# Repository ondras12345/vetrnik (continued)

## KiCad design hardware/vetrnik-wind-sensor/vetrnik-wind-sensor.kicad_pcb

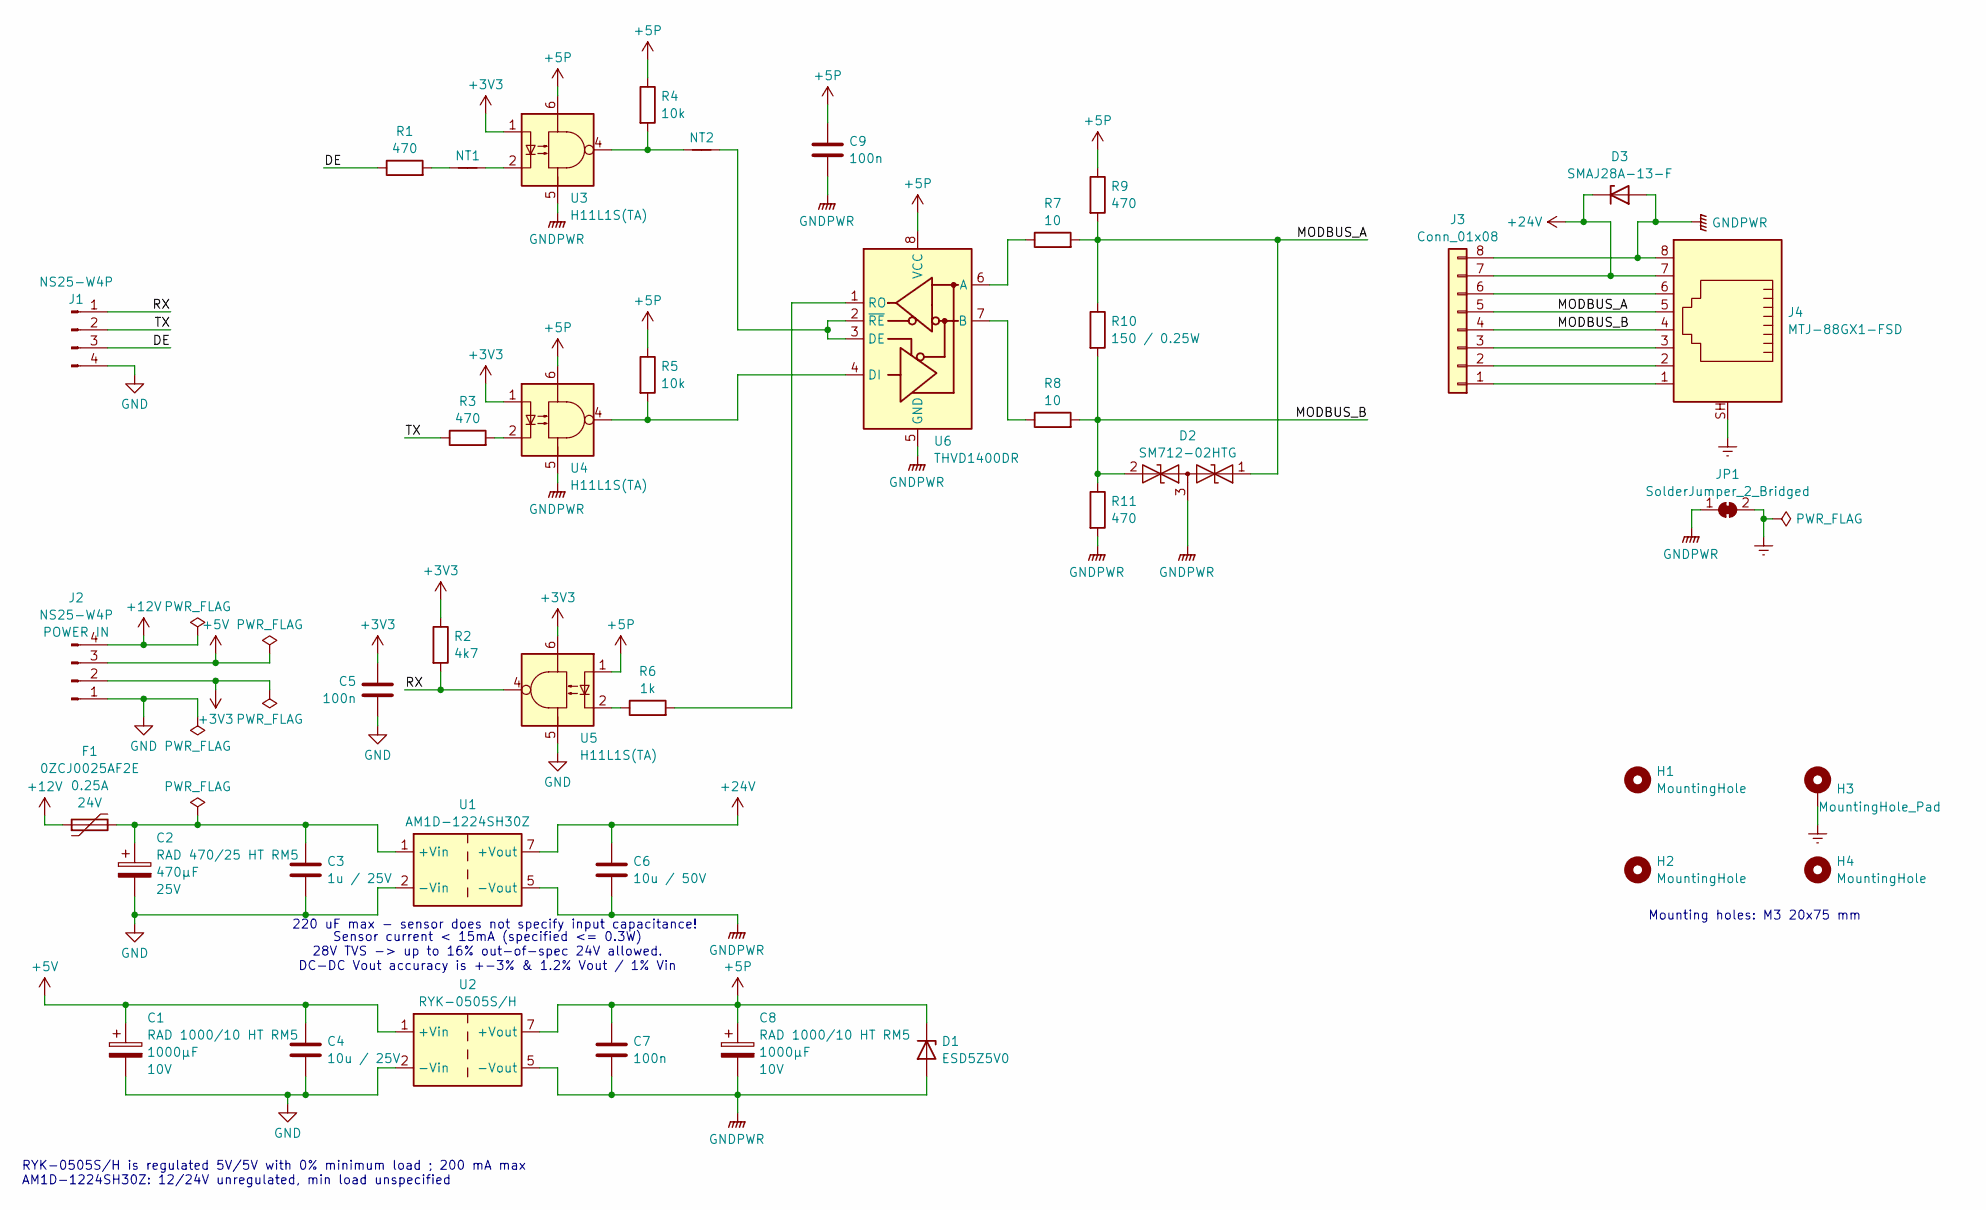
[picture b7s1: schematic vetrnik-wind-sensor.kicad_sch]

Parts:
C1, C8: RAD 1000/10 HT RM5; CP_Radial_D8.0mm_P5.00mm; Rated Voltage 10V
C2: RAD 470/25 HT RM5; CP_Radial_D10.0mm_P5.00mm; Rated Voltage 25V
C3: 1u / 25V; C_1206_3216Metric_Pad1.33x1.80mm_HandSolder
C4: 10u / 25V; C_1206_3216Metric_Pad1.33x1.80mm_HandSolder
C5, C7, C9: 100n; C_1206_3216Metric_Pad1.33x1.80mm_HandSolder
C6: 10u / 50V; C_1206_3216Metric_Pad1.33x1.80mm_HandSolder
D1: ESD5Z5V0; D_SOD-523; Breakdown Voltage 6.2V; Forward Voltage 6.2V
D2: SM712-02HTG; SOT-23; Breakdown Voltage 7.5...13.3V; Forward Voltage 7.5...13.3V
D3: SMAJ28A-13-F; D_SMA_Handsoldering; Breakdown Voltage 31.1...34.4V; Forward Voltage 31.1...34.4V
F1: 0ZCJ0025AF2E; Fuse_1206_3216Metric_Pad1.42x1.75mm_HandSolder; Rated Voltage 24V
H1, H2, H4: MountingHole; MountingHole_3.2mm_M3
H3: MountingHole_Pad; MountingHole_3.2mm_M3_Pad
J1, J2: NS25-W4P; Molex_KK-254_AE-6410-04A_1x04_P2.54mm_Vertical; Rated Voltage 0.25kV
J3: Conn_01x08; PinHeader_1x08_P2.54mm_Vertical
J4: MTJ-88GX1-FSD; RJ45_HALO_HFJ11-x2450HRL_Horizontal
JP1: SolderJumper_2_Bridged; R_1206_3216Metric_Pad1.30x1.75mm_HandSolder
NT1, NT2: NetTie_2; R_1206_3216Metric_Pad1.30x1.75mm_HandSolder
R1, R3, R9, R11: 470; R_1206_3216Metric_Pad1.30x1.75mm_HandSolder
R2: 4k7; R_1206_3216Metric_Pad1.30x1.75mm_HandSolder
R4, R5: 10k; R_1206_3216Metric_Pad1.30x1.75mm_HandSolder
R6: 1k; R_1206_3216Metric_Pad1.30x1.75mm_HandSolder
R7, R8: 10; R_1206_3216Metric_Pad1.30x1.75mm_HandSolder
R10: 150 / 0.25W; R_1206_3216Metric_Pad1.30x1.75mm_HandSolder
U1: AM1D-1224SH30Z; Converter_DCDC_TRACO_TEA1-xxxxHI_THT; Input Voltage 10.8...13.2V DC; Output Voltage 24V DC
U2: RYK-0505S/H; Converter_DCDC_TRACO_TEA1-xxxxHI_THT; Input Voltage 5V DC; Output Voltage 5V DC
U3, U4, U5: H11L1S(TA); SMDIP-6_W9.53mm
U6: THVD1400DR; SOIC-8_3.9x4.9mm_P1.27mm; Supply Voltage 3...5.5V DC

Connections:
+3V3: C5.1, J2.2, R2.1, U3.1, U4.1, U5.6
+5P: C7.1, C8.1, C9.1, D1.1 (K), R4.1, R5.1, R9.1, U2.7 (+Vout), U3.6, U4.6, U5.1, U6.8 (VCC)
+5V: C1.1, C4.1, J2.3, U2.1 (+Vin)
+12V: F1.1, J2.4
+24V: C6.1, D3.1 (K), J3.7, J4.7, U1.7 (+Vout)
/DE: J1.3, R1.1
/MODBUS_A: D2.1 (A1), J3.5, J4.5, R7.2, R9.2, R10.1
/MODBUS_B: D2.2 (A2), J3.4, J4.4, R8.2, R10.2, R11.1
/RX: J1.1, R2.2, U5.4
/TX: J1.2, R3.1
Earth: H3.1, J4.SH, JP1.2 (B)
GND: C1.2, C2.2, C3.2, C4.2, C5.2, J1.4, J2.1, U1.2 (-Vin), U2.2 (-Vin), U5.5
GNDPWR: C6.2, C7.2, C8.2, C9.2, D1.2 (A), D2.3 (common), D3.2 (A), J3.8, J4.8, JP1.1 (A), R11.2, U1.5 (-Vout), U2.5 (-Vout), U3.5, U4.5, U6.5 (GND)
unnamed: J3.1, J4.1
unnamed: J3.2, J4.2
unnamed: J3.3, J4.3
unnamed: J3.6, J4.6
unnamed: NT1.1, R1.2
unnamed: NT1.2, U3.2
unnamed: NT2.1, R4.2, U3.4
unnamed: R3.2, U4.2
unnamed: R6.1, U5.2
unnamed: C2.1, C3.1, F1.2, U1.1 (+Vin)
unnamed: R7.1, U6.6 (A)
unnamed: R8.1, U6.7 (B)
unnamed: NT2.2, U6.2 (~RE), U6.3 (DE)
unnamed: R5.2, U4.4, U6.4 (DI)
unnamed: R6.2, U6.1 (RO)

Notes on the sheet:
Sensor current < 15mA (specified <= 0.3W) 28V TVS -> up to 16% out-of-spec 24V allowed. DC-DC Vout accuracy is +-3% & 1.2% Vout / 1% Vin
RYK-0505S/H is regulated 5V/5V with 0% minimum load ; 200 mA max AM1D-1224SH30Z: 12/24V unregulated, min load unspecified
Mounting holes: M3 20x75 mm
220 uF max - sensor does not specify input capacitance!

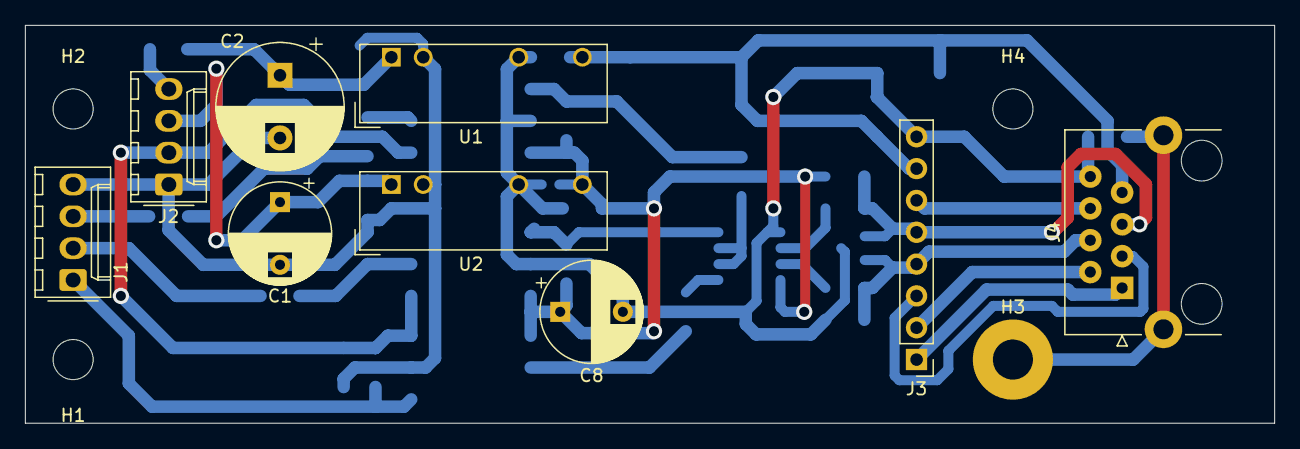
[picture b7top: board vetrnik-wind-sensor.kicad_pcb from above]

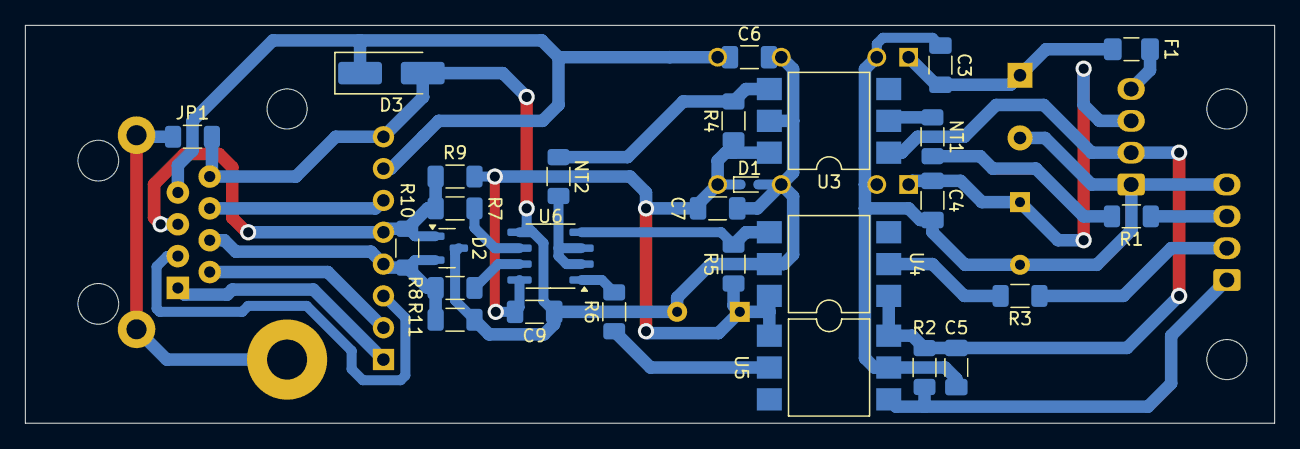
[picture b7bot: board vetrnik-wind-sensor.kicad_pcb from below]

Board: 2 copper layers, 99.7 x 31.8 mm, 41 parts (28 on the bottom side), 28 nets.

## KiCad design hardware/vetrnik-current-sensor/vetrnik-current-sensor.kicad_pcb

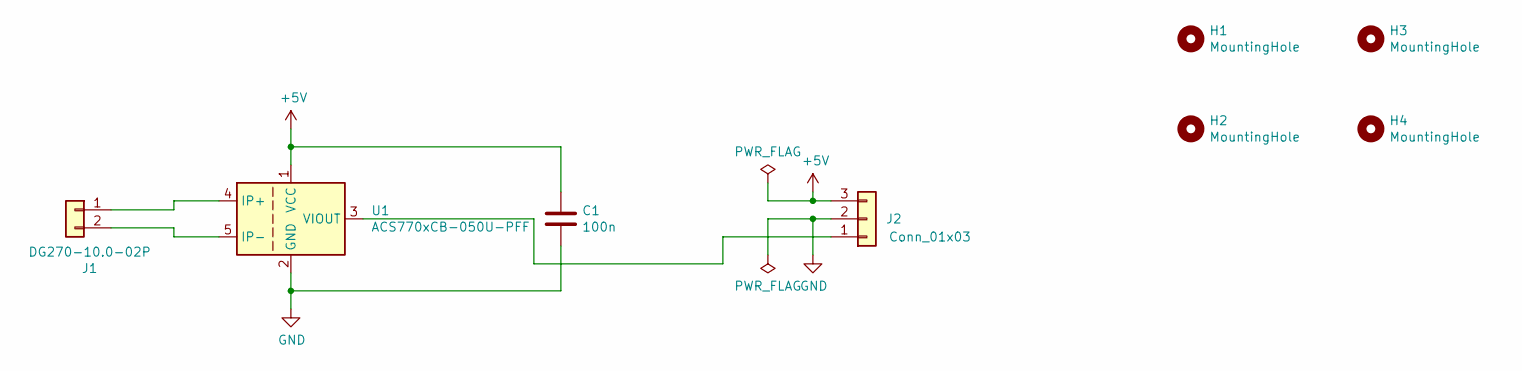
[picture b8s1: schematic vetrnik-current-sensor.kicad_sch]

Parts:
C1: 100n; C_1206_3216Metric_Pad1.33x1.80mm_HandSolder
H1, H2, H3, H4: MountingHole; MountingHole_3.2mm_M3
J1: DG270-10.0-02P; DG270-10.0-02P-14-00A
J2: Conn_01x03; Molex_KK-254_AE-6410-03A_1x03_P2.54mm_Vertical
U1: ACS770xCB-050U-PFF; Allegro_CB_PFF

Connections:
+5V: C1.1, J2.3, U1.1 (VCC)
GND: C1.2, J2.2, U1.2 (GND)
unnamed: J1.1, U1.4 (IP+)
unnamed: J1.2, U1.5 (IP-)
unnamed: J2.1, U1.3 (VIOUT)

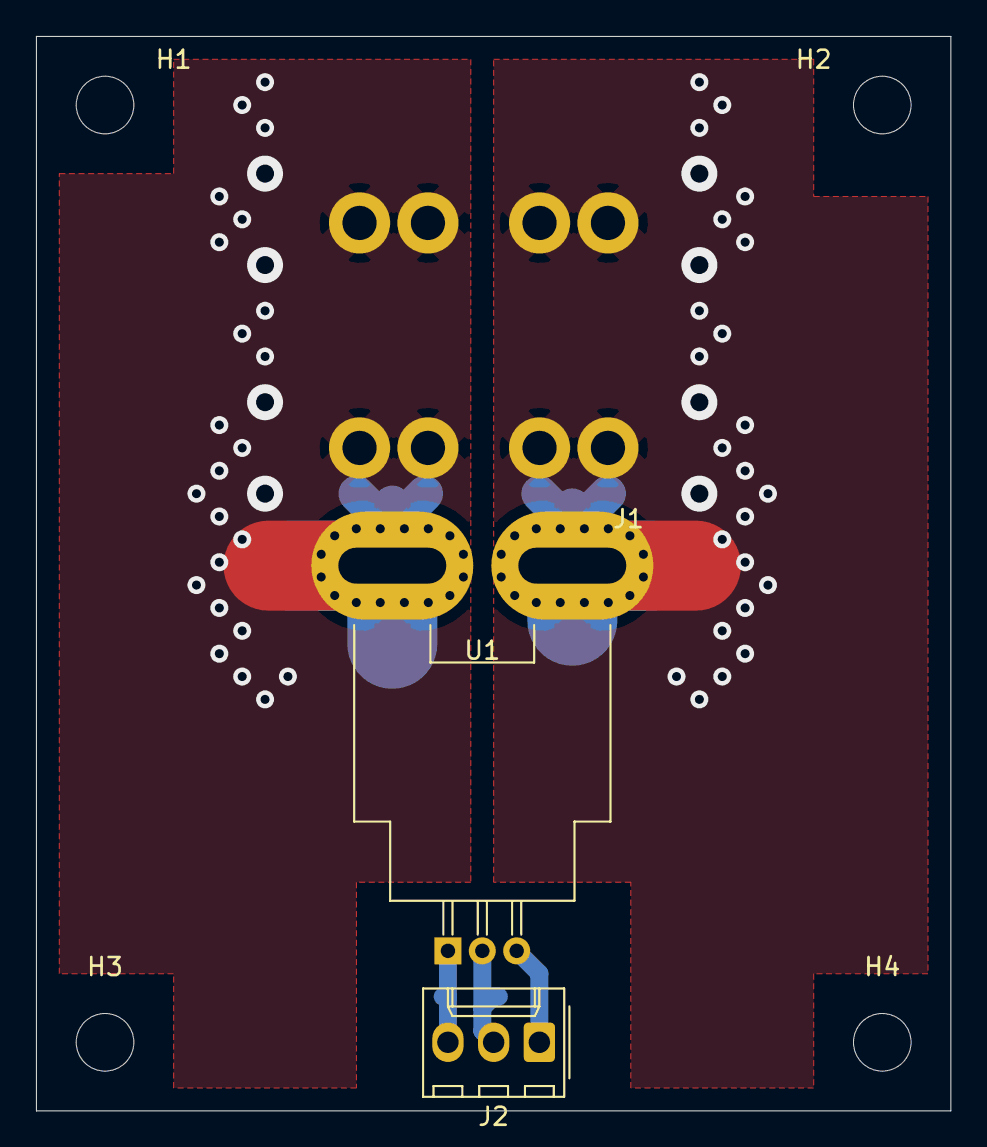
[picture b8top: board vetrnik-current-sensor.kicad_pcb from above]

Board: 2 copper layers, 50.8 x 59.7 mm, 8 parts (1 on the bottom side), 5 nets.

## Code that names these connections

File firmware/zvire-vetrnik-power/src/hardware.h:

#pragma once

#define pin_REL1        8   // PB0
#define pin_REL2        A5  // PC5
#define pin_REL3        A4  // PC4
#define pin_REL4        13  // PB5
#define pin_FAN         5   // PD5
#define pin_SHORT       6   // PD6, inverted

// See Hbridge.h
//#define pin_PWM1        9   // PB1
//#define pin_PWM2        10  // PB2
//#define pin_SD          7   // PD7, inverted

#define pin_VSENSE      A0  // PC0
#define pin_ACS712      A1  // PC1
#define pin_ACS712_2    A2  // PC2
#define pin_NTC1        A3  // PC3

// RPM is connected to two pins, but only pin_RPM_1 is used.
#define pin_RPM_1       2   // PD2
#define pin_RPM_2       4   // PD4
#define pin_ENABLE      3   // PD3, inverted

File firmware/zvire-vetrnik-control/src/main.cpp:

#include <Arduino.h>
#include "settings.h"

#ifdef WATCHDOG_TIME
#include <IWatchdog.h>
#endif

#include "uart_power.h"
#include "power_datapoints.h"
#include "mqtt.h"
#include "ota.h"
#include "cli.h"
#include "debug.h"
#include "power_board.h"
#include "lisp.h"
#include "control.h"
#include "stats.h"
#include "display.h"
#include "sensor_DS18B20.h"
#include "log.h"
#include "reset_cause.h"
#include <SerialFlash.h>
#include <Bounce2.h>


static Bounce2::Button button1 = Bounce2::Button();
static Bounce2::Button button2 = Bounce2::Button();


void setup()
{
    reset_cause_t reset_cause = reset_cause_get();
    log_init(
        reset_cause == RESET_CAUSE_BROWNOUT_RESET ||
        reset_cause == RESET_CAUSE_POWER_ON_POWER_DOWN_RESET
    );
    log_add_record_reboot(reset_cause);

    Serial.begin();
    log_add_INFO_backend(&Serial);

    button1.attach(PIN_BUTTON1, INPUT_PULLUP);
    button1.interval(BUTTON_DEBOUNCE);
    button1.setPressedState(LOW);
    button2.attach(PIN_BUTTON2, INPUT_PULLUP);
    button2.interval(BUTTON_DEBOUNCE);
    button2.setPressedState(LOW);

    pinMode(PIN_SHORT_SENSE, INPUT_PULLUP);
    pinMode(PIN_BUZZER, OUTPUT);
    pinMode(PIN_SHORT, OUTPUT);
    pinMode(PIN_LED, OUTPUT);
    // PIN_ONEWIRE is unused
    pinMode(PIN_REL1, OUTPUT);
    pinMode(PIN_REL2, OUTPUT);

    pinMode(PIN_ETH_RST, OUTPUT);
    ETH_reset();

    digitalWrite(PIN_BUZZER, HIGH);
    pinMode(LED_BUILTIN, OUTPUT);
    for (uint8_t i = 0; i < 4; i++)
    {
        digitalWrite(LED_BUILTIN, LOW);
        delay(100);
        digitalWrite(LED_BUILTIN, HIGH);
        delay(100);
    }
    INFO->print("Flash init: ");
    INFO->println(SerialFlash.begin(PIN_FLASH_SS));
    INFO->println("settings_init");
    INFO->flush();
    settings_init();
    INFO->flush();
    MQTT_init();
#ifdef WATCHDOG_TIME
    // Only do this after MQTT_init (DHCP is slow)
    IWatchdog.begin(WATCHDOG_TIME*1000UL);
#endif
    uart_power_init();
    control_init();
    sensor_DS18B20_init();
    lisp_init();
    control_init_lisp();
    INFO->println("boot");
    CLI_init();
    display_init();
    display_init_lisp();
    lisp_run_blind_file(LISP_INIT_FILENAME);

    digitalWrite(PIN_BUZZER, LOW);
}


void loop()
{
    unsigned long loop_start_millis = millis();
    button1.update();
    if (button1.released())
    {
        if (button1.previousDuration() < BUTTON_LONG)
        {
            lisp_run_blind("(btn1_short)");
        }
        else if (button1.previousDuration() >= BUTTON_LONG)
        {
            lisp_run_blind("(btn1_long)");
        }
    }
    button2.update();
    if (button2.released())
    {
        if (button2.previousDuration() < BUTTON_LONG)
        {
            lisp_run_blind("(btn2_short)");
        }
        else if (button2.previousDuration() >= BUTTON_LONG)
        {
            lisp_run_blind("(btn2_long)");
        }
    }

    power_datapoints_loop();
    bool status_complete = uart_power_loop();
    if (status_complete)
    {
        power_board_status = power_board_status_read();
        control_new_state();
        stats_new_state();
        static bool prev_emergency = false;
        if (power_board_status.emergency != prev_emergency)
        {
            prev_emergency = power_board_status.emergency;
            log_add_event(kPowerBoardEmergency);
        }
    }
    else if (power_board_status.valid &&
             millis() - power_board_status.retrieved_millis >= 2000UL)
    {
        log_add_event_and_println(kPowerBoardStatusTimeout, INFO);
        power_board_status.valid = false;
        control_new_state();
        stats_new_state();
    }

    sensor_DS18B20_loop();
    control_loop();
    CLI_loop();
    unsigned long loop_duration_mid = millis() - loop_start_millis;
    MQTT_loop();
    ota_loop();
    display_loop();

    unsigned long loop_duration = millis() - loop_start_millis;
    if (loop_duration >= 1500U)
    {
        log_add_record_slow_loop(loop_duration, loop_duration_mid);
    }

#ifdef WATCHDOG_TIME
    IWatchdog.reload();
#endif
}

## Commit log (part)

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2023-01-30 [control] Add lisp commands for control strategy
2023-01-30 [power] Faster ADC sampling
2023-01-30 [power] Disable debug mode
2023-01-31 [power] Move RMS filter processing to ISR
    | conditions | before | after |
    |:--------------|:----------------|:----------------|
    | d128 with cap | 10.370A (1.030) | 10.065A (1.007) |
    | d128 w/o cap | 10.614A (0.936) | 10.065A (0.936) |
    | d255 with cap | 16.653A (1.671) | 16.592A (1.661) |
    | d255 w/o cap | 16.531A (1.651) | 16.470A (1.647) |
2023-01-31 [control] Rename `mqtt_status` CLI cmnd to `mqtt`
2023-01-31 [control] Rename Stream_utils to Print_utils
2023-02-01 [control] Add Lisp handler functions for buttons
2023-02-03 [hardware] Add control board schematics
2023-02-04 [hardware] Design other PCBs
2023-02-08 [control] Set up GPIO outputs
2023-02-08 [control] Add #define for Ethernet reset pin
2023-02-08 [control] Set LCD backlight from lisp
2023-02-08 [control] Restore fe (lisp) gc after error
2023-02-08 [control] Control LED_BUILTIN from lisp
2023-02-09 [control] Improve error message in CLI
2023-02-09 [control] Set duty to 0 when started by btn1_long
2023-02-09 [control] Use ethernet reset pin
    Mostly just to prevent issues with noise that might occur when it's left
    floating.
    Even touching the pin with a DMM probe would cause a reset.
2023-02-09 [hardware] Resistor values in current-sensor-opamp
2023-02-10 [control] Improve MPPT algorithm
2023-02-11 [control] Update shellminator & commander
2023-02-12 [control] Make startup faster
2023-03-05 [power] Report emergency mode status
2023-03-05 [control] Support power board emergency mode
2023-03-09 [control] Automatically reset ETH if it gets stuck
2023-04-08 [control] Sense contactor state and handle e-stop
2023-04-08 Add info about contactor RC snubber
2023-04-28 [power] Optimize for code size
2023-04-28 [power] Use ATOMIC_BLOCK instead of saving SREG
2023-04-28 [power] Replace cli/sei with ATOMIC_FORCEON
2023-04-28 [power] Use avr/eeprom.h instead of Arduino EEPROM
    This saves about 192 bytes of FLASH space.
2023-04-28 [power] Add puncover target to Makefile
2023-04-28 [power] Reduce number of millis calls
2023-04-29 [power] Add settings for OCP limits
2023-04-29 [power] Update NTC immediately after boot
2023-04-29 [control] Add support for power board REL outputs
2023-04-29 [control] Add info about telnet to README.md
2023-04-29 [control] Update TODOs in lisp/31-control-MPTT
2023-06-16 [control] Add hysteresis to MQTT RPM
2023-06-25 [control] Group MQTT topics for temperatures
2023-07-17 [hardware] Add gitignore file
2023-07-17 [control] Publish DS18B20 temperatures via MQTT
2023-07-17 [control] Add initial support for DS18B20 sensors
2023-07-17 [control] Give fe more memory
    I didn't encounter any problems, but after experimenting with
    test_fe_utils I found that 8k might be pushing it.
    More memory should allow the GC to run less often.
2023-07-18 [control] Add rem test case to test_fe_utils
2023-07-18 [control] Add basic support for OTA fw update
2023-07-19 [power] Add software enable command
2023-07-19 [control] Fix CLIeditor end sequence detection
2023-07-21 [control] [LISP] Control sw_enable & pump
2023-07-24 [LISP] Fix error if t0 temperature is nil
2023-07-24 [control] Report power_board/power via MQTT
2023-07-25 [control] Fix MAKETMP_DECIMAL for uint32_t
2023-07-27 [hardware] Add info about cables
2023-07-27 [control] Update dependencies
2023-07-28 [control] Optimize MAKETMP_BOOL MQTT helper
2023-07-29 [control] Allow executing CLI commands via MQTT
2023-08-07 [control] Add Home Assistant config package
2023-08-16 [power] Make RPM filter configurable
2023-08-16 [power] Improve build system
2023-08-16 [power] Remove TODO comment
2023-08-30 [control] Quiet down HA notification automation
2023-09-01 Silence warnings from new version of cppcheck
2023-09-01 [control] Reduce socket timeout for MQTT
    This should hopefully allow us to respond to the power board in time.
2023-09-05 [control] Add first version of postmort
2023-09-05 [control] Fix printf format strings
2023-09-05 [control] Enable -Wall compiler warnings
2023-09-06 [control] Only print first 100 records in CLI log
2023-09-06 [control] Fix log printing bug
2023-09-17 [control] Log DS18B20 errors
2023-09-30 [control] Update HA configuration for 2023.9
2023-11-12 [control] Add id to HA automation
2023-12-08 Rename firmware projects
2023-12-08 Remove outdated gbrjob files
2023-12-08 Rename enclosure documentation
2023-12-08 Update README files
2023-12-22 [control] Fix printing of MQTT publish error log
2023-12-22 [control] Detect & log millis rollover
2023-12-22 [control] Fix potentially imprecise energy stats
2023-12-22 [control] Log last millis value before reset
2023-12-22 [control] Prevent immediate MQTT reconnect
2023-12-22 [control] Add energy_Ws to Home Assistant
2024-03-23 [control] Make reset cause name shorter
    The kReboot message wouldn't fit in 80-character buffer in log.cpp
2024-04-07 [hardware] Fix renamed library
2024-04-10 [hardware] Add info about enclosure mods
2024-06-25 Add patch for testing w/o DS18B20
2024-06-26 [control] Implement smarter contactor control
2024-06-26 [LISP] Check power mode in btn1_long
2024-06-26 [control] Refactor conf printing and parsing
2024-06-26 [control] Store settings in text file
2024-06-26 [control] Fix false error raised from LISP ctrls
2024-06-26 [control] Tolerate 0x00 at the start of init.lisp
2024-06-26 [control] Split SPIflash to multiple commands
    before split:
    RAM: [======= ] 67.1% (used 44004 bytes from 65536 bytes)
    Flash: [===== ] 48.6% (used 127396 bytes from 262144 bytes)
    after split:
    RAM: [======= ] 67.5% (used 44220 bytes from 65536 bytes)
    Flash: [===== ] 48.7% (used 127740 bytes from 262144 bytes)
2024-06-27 [control] Fix parsing of DS18B20 config
    It would fail to parse after dfu upload, was reading uninitialized
    memory.
2024-06-27 [power] Report reset reason on boot
2024-06-27 [power] Add setting for stopping RPM
2024-06-27 [control] Try to fix WDT reset on mqtt reinit
2024-06-27 [control] Fix cat sometimes drops start of line
2024-06-27 [power] Tolerate longer refresh interval
2024-06-27 [power] Fix PWM generation
2024-06-28 [power] Add info from RPM filter measurement
    This was measured with DC offset on Meratronik gen to ensure enough
    amplitude for 50 % duty at optocoupler output.
2024-06-28 [LISP] Update instructions
2024-06-28 [LISP] MQTT reinit via btn2_long
2024-07-02 [power] Update OVP constants
    Hardware OVP trip voltage was changed in last HW mod, this commit
    updates SW OVP accordingly.
2024-07-02 [control] Update settings comment
2024-08-23 [hardware] Add block diagram
2024-08-23 [hardware] Add block diagram PDF
2025-02-01 Update pre-commit-hooks
2025-02-01 Add flake8 check to pre-commit
2025-02-01 Add yamllint check to pre-commit
2025-02-01 Add more LISP tests
2025-02-01 Port fe_utils from C++ to C
2025-02-02 Move display lisp functions to a separate lib
2025-02-02 Use t instead of 1 as true value in LISP tests
2025-02-02 Fix incorrect LISP test
    Discovered by
    $ ./sil.py run ../vetrnik-control/lisp/tests/test_*.lisp
2025-02-02 Add missing header in SIL
    sil.py needs it
2025-02-02 Add more functions to SIL
2025-02-04 Add custom Modelica tools
2025-02-05 Create a Modelica package
2025-02-05 Set rectifier parameters in test3
    Setting Goff=2.5e-8 S results in extremely slow simulation,
    so I'll leave it off for now.
2025-02-06 Add function to call vetrnik-sil from Modelica
2025-02-06 Add implement '(ds18' in SIL
2025-02-06 Add model README
2025-02-07 Make lines in WindTurbine model shorter
2025-02-08 Improve diagram of test4 model
2025-02-10 Fix rectifier parameters in SIL model
2025-02-11 Add icon to vetrnikController
2025-02-13 [LISP] Improve MPPT
    ... based on SILsimplified simulations.
    However, the original algorithm might have some advantages.
    It might be able to operate with a higher sampling rate.
2025-02-17 [LISP] Fix incorrect spec for pwrg
2025-02-21 Increase LISP memory size
2025-02-21 Improve MQTT_reinit watchdog fix
2025-02-21 Retry Ethernet even if eth_skip
2025-02-21 Fix missing pinMode in sensor_wind
2025-02-21 Handle errors in SIL REPL
2025-02-22 Add missing header include to reset_cause
    This will prevent the build from failing when ststm32 is updated.
    ststm32@15.6.0
    RAM: [======== ] 81.5% (used 53396 bytes from 65536 bytes)
    Flash: [===== ] 49.6% (used 129944 bytes from 262144 bytes)
    ststm32@16.0.0
    RAM: [======== ] 81.5% (used 53396 bytes from 65536 bytes)
2025-02-22 [power] Increase duty gradually in stopping mode
2025-02-23 [power] Do not require enable to start
2025-02-23 [control] Support larger MQTT messages
2025-03-01 Add temperature sensor to block diagram
    ...and rotate "G" in the generator symbol
2025-04-05 [model] Add diagrams to gitignore
2025-04-05 [model] Add SimplifiedOpenLoopTest.mo
2025-04-05 [model] Enable raiseerrors in linearize.py
2025-04-06 [model] Move Result to a separate .py file
    This should make it possible to import without having OMPython
    installed.
2025-04-06 [model] Add tool for diffing linearized models
2025-04-12 [model] Add models from testing
    I've created these quite some time ago, and while they aren't
    immediately useful, I don't want to delete them.
2025-04-12 Rename modes
2025-04-12 [lisp] Add test for (pwrs "mode" ...)
2025-04-12 Rename power modes in homeassistant config
2025-04-12 [control] s/PIN_SHORT_SENSE/PIN_CONTACTOR_SENSE/
2025-04-12 [control] Rename kControlShortEstop to kControlEstop
2025-04-12 [control] Use HAL functions in CLI
    before:
    RAM: [======== ] 81.5% (used 53392 bytes from 65536 bytes)
    Flash: [===== ] 49.6% (used 130136 bytes from 262144 bytes)
    after:
    RAM: [======== ] 81.5% (used 53392 bytes from 65536 bytes)
    Flash: [===== ] 49.7% (used 130200 bytes from 262144 bytes)
2025-04-12 [control] Update architecture overview in README
2025-04-18 [model] Add model for SIL with CSV input
2025-04-18 [control] Add pow function to lisp
2025-04-19 [lisp] Use a symlink to select MPPT controller
    Renaming files to *.disabled does not play nice with git.
2025-04-19 [control] Reduce flash usage
    ... by concatenating topic strings at runtime
    before:
    RAM: [======== ] 81.5% (used 53400 bytes from 65536 bytes)
    Flash: [===== ] 50.7% (used 132948 bytes from 262144 bytes)
    after:
    RAM: [======== ] 81.5% (used 53400 bytes from 65536 bytes)
2025-04-19 [control] Reduce flash usage
    before:
    RAM: [======== ] 81.5% (used 53412 bytes from 65536 bytes)
    Flash: [===== ] 50.7% (used 132796 bytes from 262144 bytes)
    after:
    RAM: [======== ] 81.5% (used 53412 bytes from 65536 bytes)
    Flash: [===== ] 50.5% (used 132404 bytes from 262144 bytes)
2025-04-19 Revert to inline MQTT command handlers
    before:
    RAM: [======== ] 81.5% (used 53412 bytes from 65536 bytes)
    Flash: [===== ] 50.5% (used 132340 bytes from 262144 bytes)
    after:
    RAM: [======== ] 81.5% (used 53412 bytes from 65536 bytes)
    Flash: [===== ] 50.5% (used 132268 bytes from 262144 bytes)
2025-04-19 [control] Reduce flash usage in MQTT handler
    before:
    RAM: [======== ] 81.5% (used 53412 bytes from 65536 bytes)
    Flash: [===== ] 50.4% (used 132100 bytes from 262144 bytes)
    after:
    RAM: [======== ] 81.5% (used 53412 bytes from 65536 bytes)
    Flash: [===== ] 50.4% (used 132084 bytes from 262144 bytes)
2025-04-19 [control] Disable "free" CLI command to save flash
    before:
    RAM: [======== ] 81.5% (used 53412 bytes from 65536 bytes)
    Flash: [===== ] 50.0% (used 131008 bytes from 262144 bytes)
    after:
    RAM: [======== ] 81.4% (used 53340 bytes from 65536 bytes)
    Flash: [===== ] 49.5% (used 129696 bytes from 262144 bytes)
2025-04-20 [lisp] Remove debug prints from adaptive HCS
2025-04-21 [model] Add limits & anti-windup to TSR PI
2025-04-21 [lisp] Improve controller comparison data
    Best results were achieved with:
    Ts = 12.0
    SA = 3
    Ts = 8.0 for HCS-adaptive
2025-04-28 [lisp] Fix spec markdown file format
2025-04-28 [control] Increase wind speed sensor read timeout
2025-04-30 [lisp] Improve spec
2025-05-01 [hardware] Clean up vetrnik-H-bridge schematic
2025-05-01 [hardware] Clean up vetrnik-current-sensor-opamp
2025-05-01 [hardware] Clean up vetrnik-relays
2025-05-10 [model] Add scripts for SIL with Vetrnik.SILcsv
